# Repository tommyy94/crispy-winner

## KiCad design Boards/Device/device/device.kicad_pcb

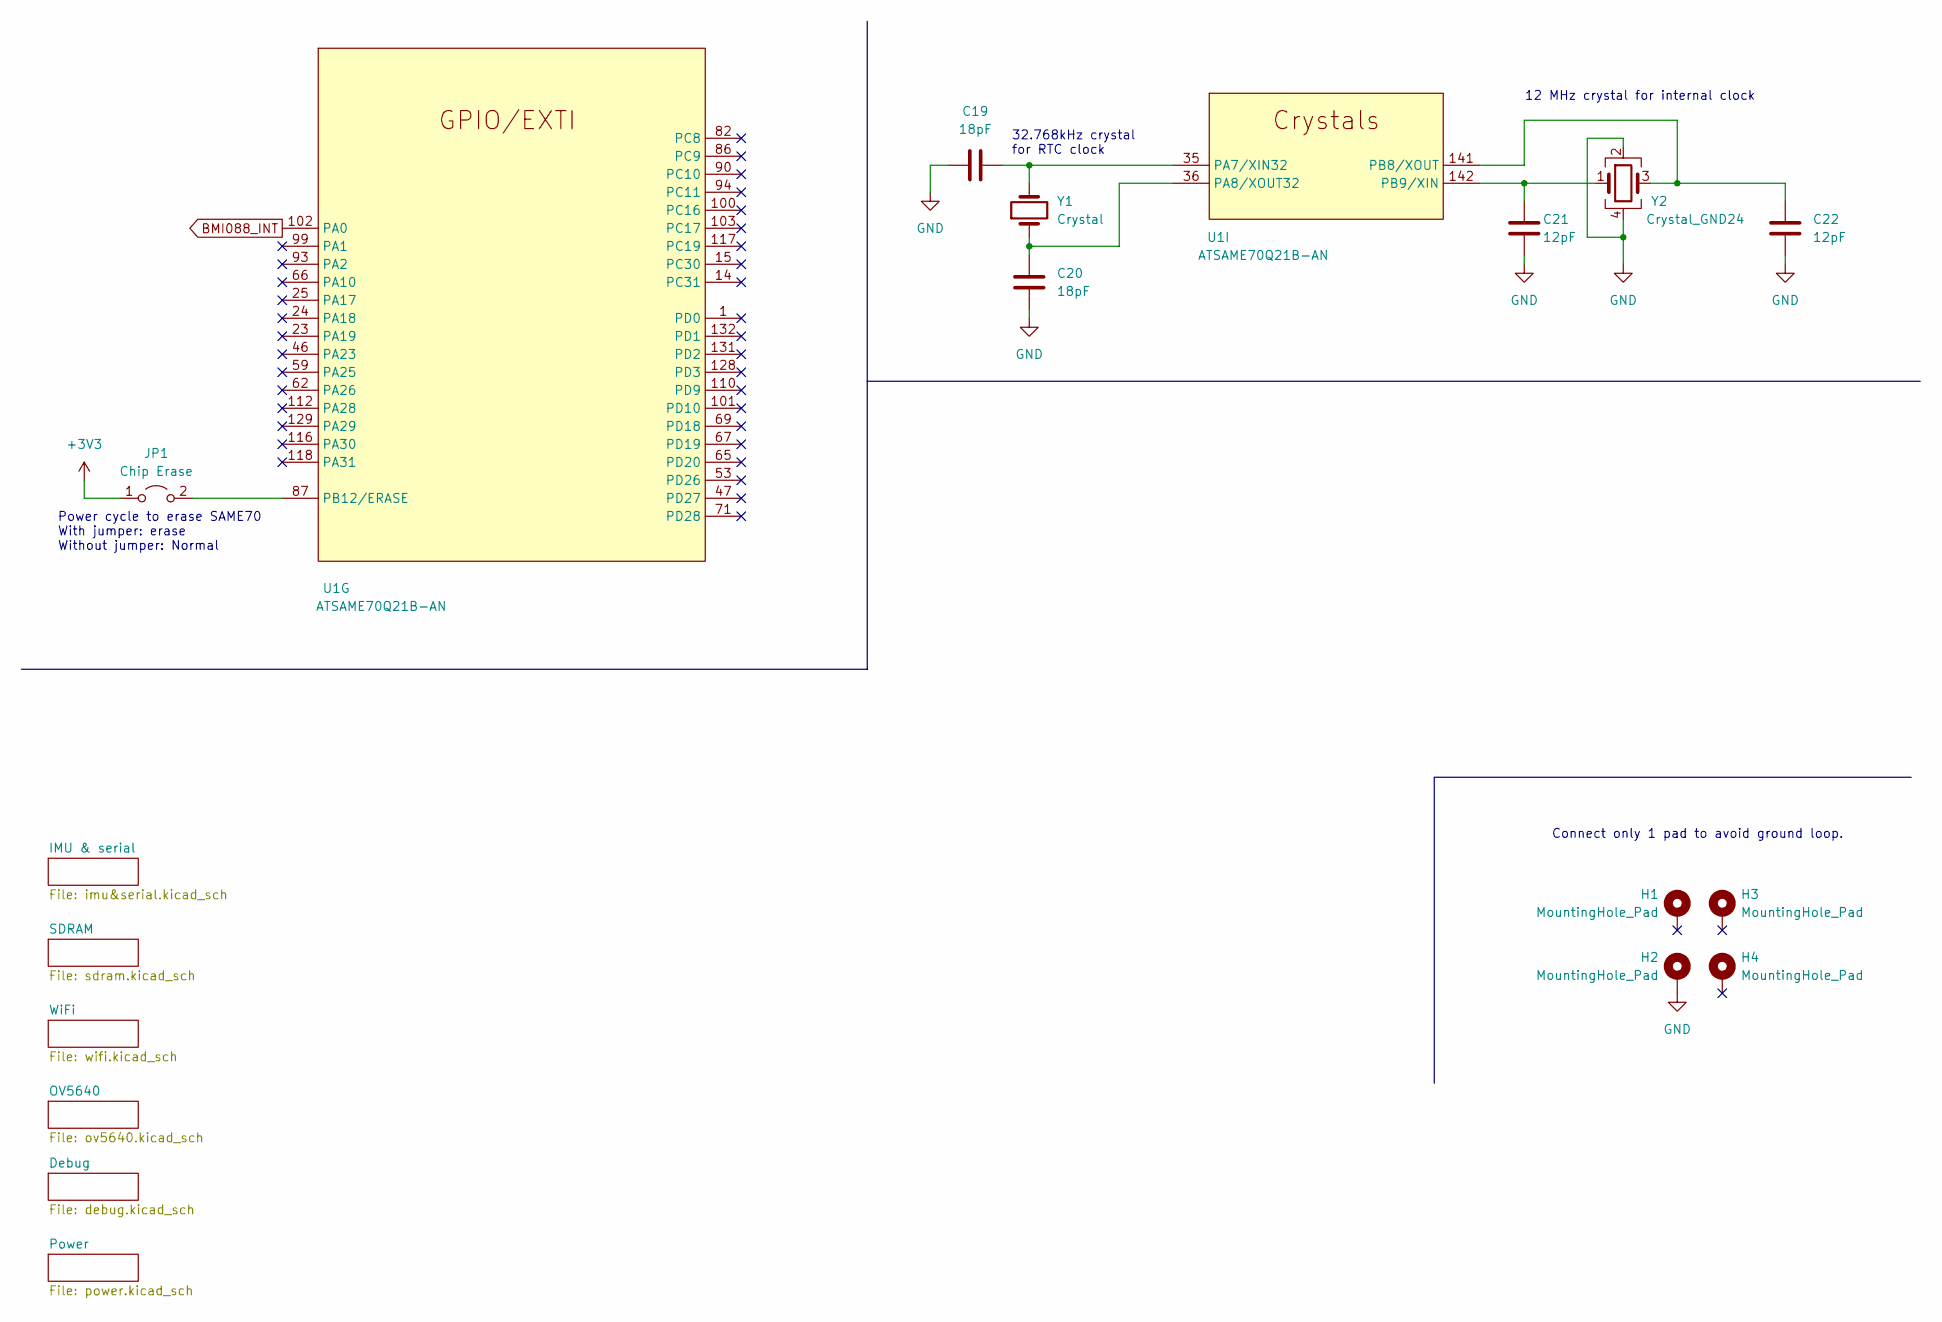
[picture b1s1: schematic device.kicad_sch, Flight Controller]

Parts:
C19, C20: 18pF; C_0603_1608Metric_Pad1.08x0.95mm_HandSolder
C21, C22: 12pF; C_0603_1608Metric_Pad1.08x0.95mm_HandSolder
H1, H2, H3, H4: MountingHole_Pad; MountingHole_3.2mm_M3_Pad
JP1: Chip Erase; PinHeader_1x02_P2.54mm_Vertical
U1: ATSAME70Q21B-AN; LQFP-144_20x20mm_P0.5mm
Y1: Crystal; Crystal_SMD_0603-2Pin_6.0x3.5mm_HandSoldering
Y2: Crystal_GND24; Crystal_SMD_0603-4Pin_6.0x3.5mm_HandSoldering

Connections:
+3V3: JP1.1 (A); also elsewhere on the board
BMI088_INT: U1.102 (PA0); also elsewhere on the board
GND: C19.1, C20.1, C21.2, C22.2, H2.1, Y2.2, Y2.4; also elsewhere on the board
unnamed: C19.2, U1.35 (PA7/XIN32), Y1.2
unnamed: C20.2, U1.36 (PA8/XOUT32), Y1.1
unnamed: C21.1, U1.142 (PB9/XIN), Y2.1
unnamed: C22.1, U1.141 (PB8/XOUT), Y2.3
unnamed: JP1.2 (B), U1.87 (PB12/ERASE)

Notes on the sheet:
Connect only 1 pad to avoid ground loop.
12 MHz crystal for internal clock
32.768kHz crystal for RTC clock
Power cycle to erase SAME70 With jumper: erase Without jumper: Normal

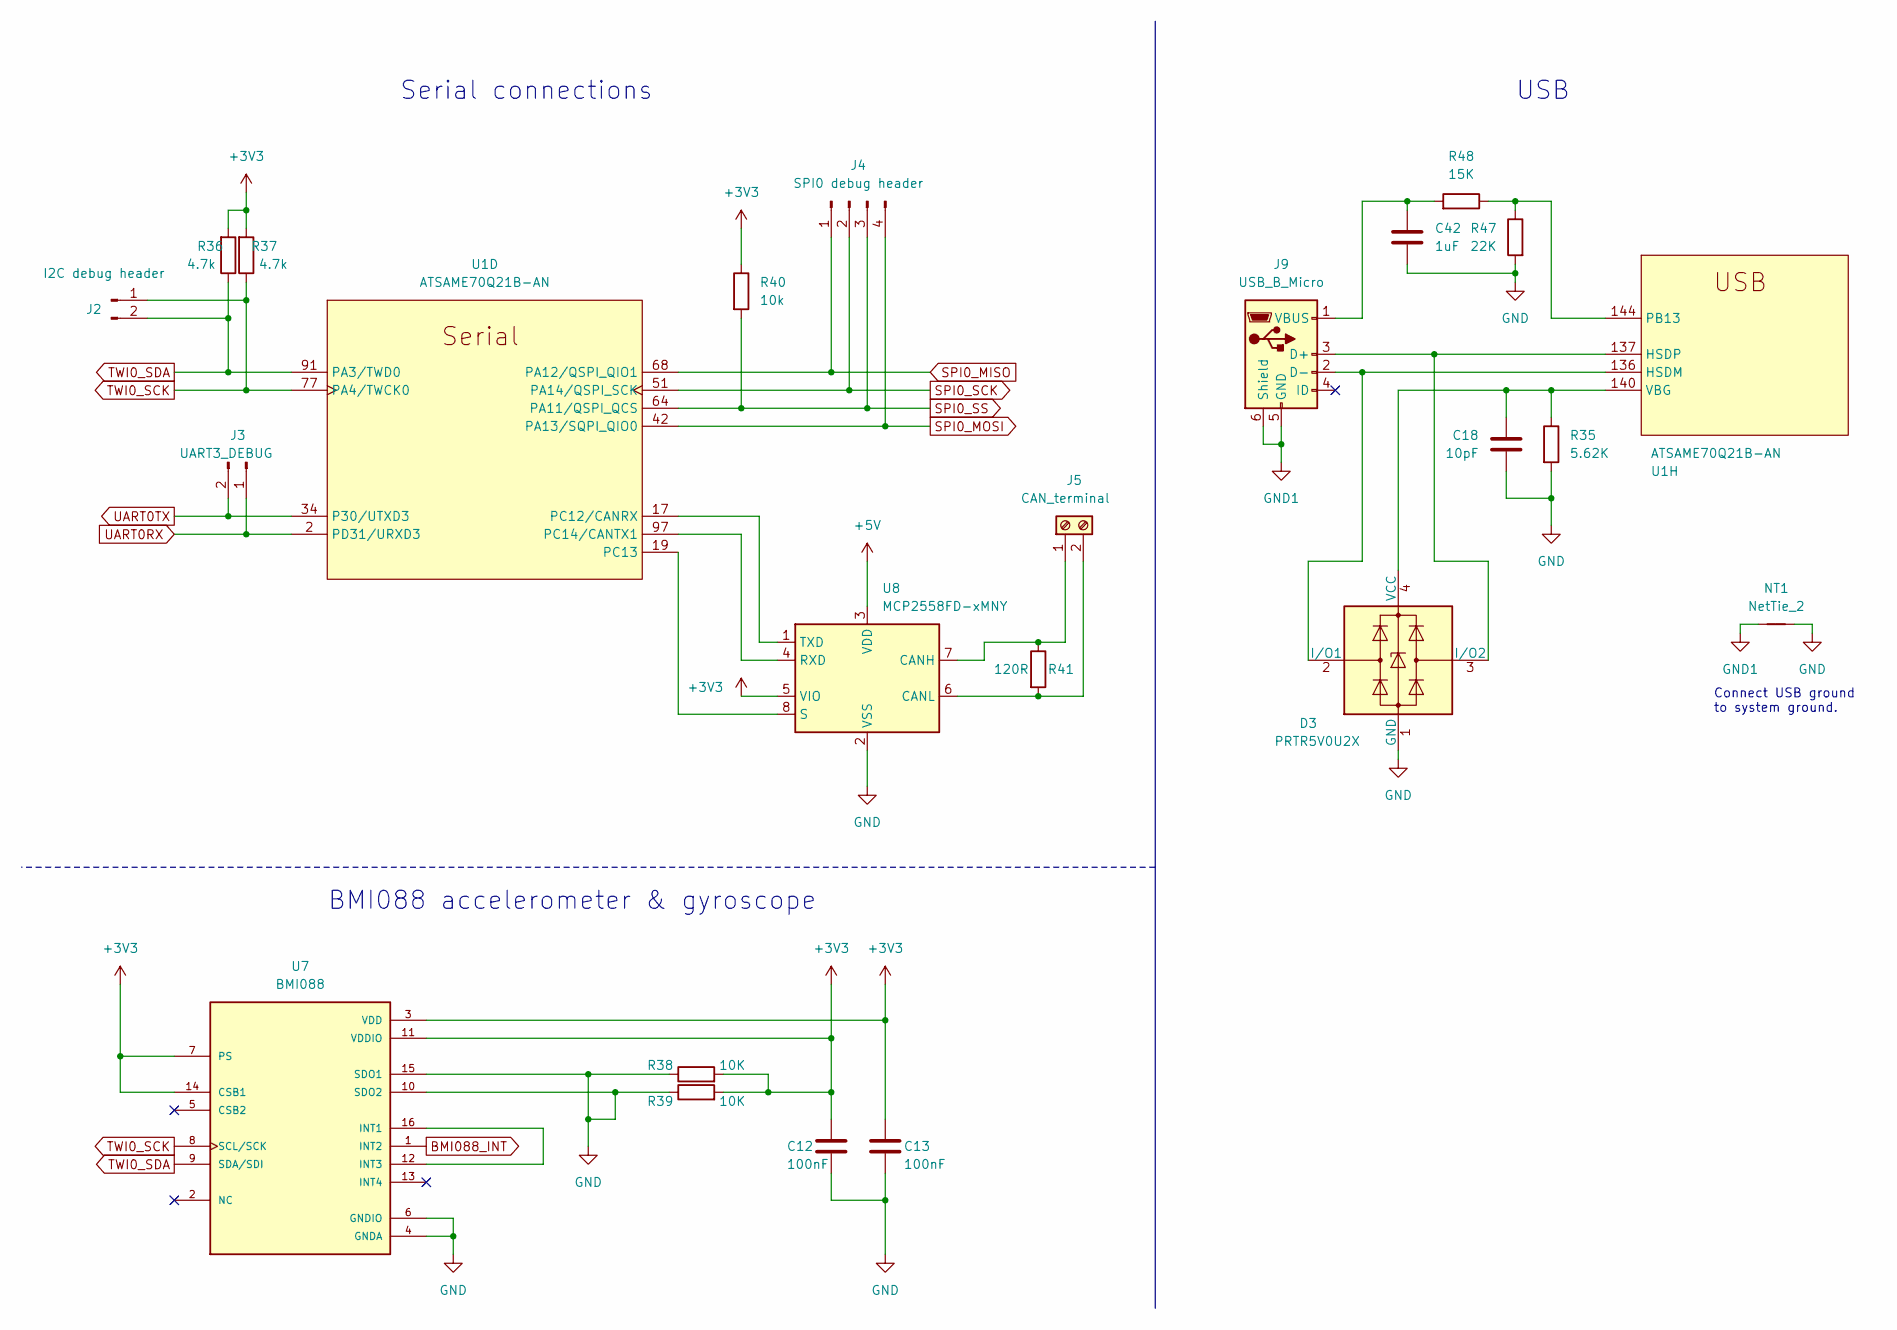
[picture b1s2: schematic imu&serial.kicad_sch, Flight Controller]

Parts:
C12, C13: 100nF; C_0603_1608Metric_Pad1.08x0.95mm_HandSolder
C18: 10pF; C_0603_1608Metric_Pad1.08x0.95mm_HandSolder
C42: 1uF; C_0603_1608Metric_Pad1.08x0.95mm_HandSolder
D3: PRTR5V0U2X; SOT-143
J2: I2C debug header; PinHeader_1x02_P2.54mm_Vertical
J3: UART3_DEBUG; PinHeader_1x02_P2.54mm_Vertical
J4: SPI0 debug header; PinHeader_1x04_P2.54mm_Vertical
J5: CAN_terminal; TerminalBlock_Altech_AK300-2_P5.00mm
J9: USB_B_Micro; USB_Micro-B_Wuerth_614105150721_Vertical
NT1: NetTie_2; NetTie-2_SMD_Pad2.0mm
R35: 5.62K; R_0201_0603Metric_Pad0.64x0.40mm_HandSolder
R36, R37: 4.7k; R_0201_0603Metric_Pad0.64x0.40mm_HandSolder
R38, R39: 10K; R_0201_0603Metric_Pad0.64x0.40mm_HandSolder
R40: 10k; R_0201_0603Metric_Pad0.64x0.40mm_HandSolder
R41: 120R; R_0201_0603Metric_Pad0.64x0.40mm_HandSolder
R47: 22K; R_0201_0603Metric_Pad0.64x0.40mm_HandSolder
R48: 15K; R_0201_0603Metric_Pad0.64x0.40mm_HandSolder
U1: ATSAME70Q21B-AN; LQFP-144_20x20mm_P0.5mm
U7: BMI088; PQFN50P450X300X100-16N
U8: MCP2558FD-xMNY; TDFN-8-1EP_3x2mm_P0.5mm_EP1.80x1.65mm

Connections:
+3V3: C12.1, C13.1, R36.2, R37.2, R38.2, R39.2, R40.1, U7.3 (VDD), U7.7 (PS), U7.11 (VDDIO), U7.14 (CSB1), U8.5 (VIO); also elsewhere on the board
+5V: U8.3 (VDD); also elsewhere on the board
BMI088_INT: U7.1 (INT2); also elsewhere on the board
GND: C12.2, C13.2, C18.1, C42.2, D3.1 (GND), NT1.2, R35.2, R38.1, R39.1, R47.2, U7.4 (GNDA), U7.6 (GNDIO), U7.10 (SDO2), U7.15 (SDO1), U8.2 (VSS), U8.9 (VSS); also elsewhere on the board
GND1: J9.5 (GND), J9.6 (Shield), NT1.1
unnamed: C18.2, D3.4 (VCC), R35.1, U1.140 (VBG)
unnamed: D3.2 (I/O1), J9.2 (D-), U1.136 (HSDM)
unnamed: D3.3 (I/O2), J9.3 (D+), U1.137 (HSDP)
unnamed: J5.1, R41.1, U8.7 (CANH)
unnamed: J5.2, R41.2, U8.6 (CANL)
unnamed: C42.1, J9.1 (VBUS), R48.2
unnamed: R47.1, R48.1, U1.144 (PB13)
unnamed: U1.17 (PC12/CANRX), U8.1 (TXD)
unnamed: U1.19 (PC13), U8.8 (S)
unnamed: U1.97 (PC14/CANTX1), U8.4 (RXD)
unnamed: U7.12 (INT3), U7.16 (INT1)
SPI0_MISO: J4.1, U1.68 (PA12/QSPI_QIO1); also elsewhere on the board
SPI0_MOSI: J4.4, U1.42 (PA13/SQPI_QIO0); also elsewhere on the board
SPI0_SCK: J4.2, U1.51 (PA14/QSPI_SCK); also elsewhere on the board
SPI0_SS: J4.3, R40.2, U1.64 (PA11/QSPI_QCS); also elsewhere on the board
TWI0_SCK: J2.1, R37.1, U1.77 (PA4/TWCK0), U7.8 (SCL/SCK); also elsewhere on the board
TWI0_SDA: J2.2, R36.1, U1.91 (PA3/TWD0), U7.9 (SDA/SDI); also elsewhere on the board
UART0RX: J3.1, U1.2 (PD31/URXD3); also elsewhere on the board
UART0TX: J3.2, U1.34 (P30/UTXD3); also elsewhere on the board

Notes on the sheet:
USB
BMI088 accelerometer & gyroscope
Connect USB ground to system ground.
Serial connections

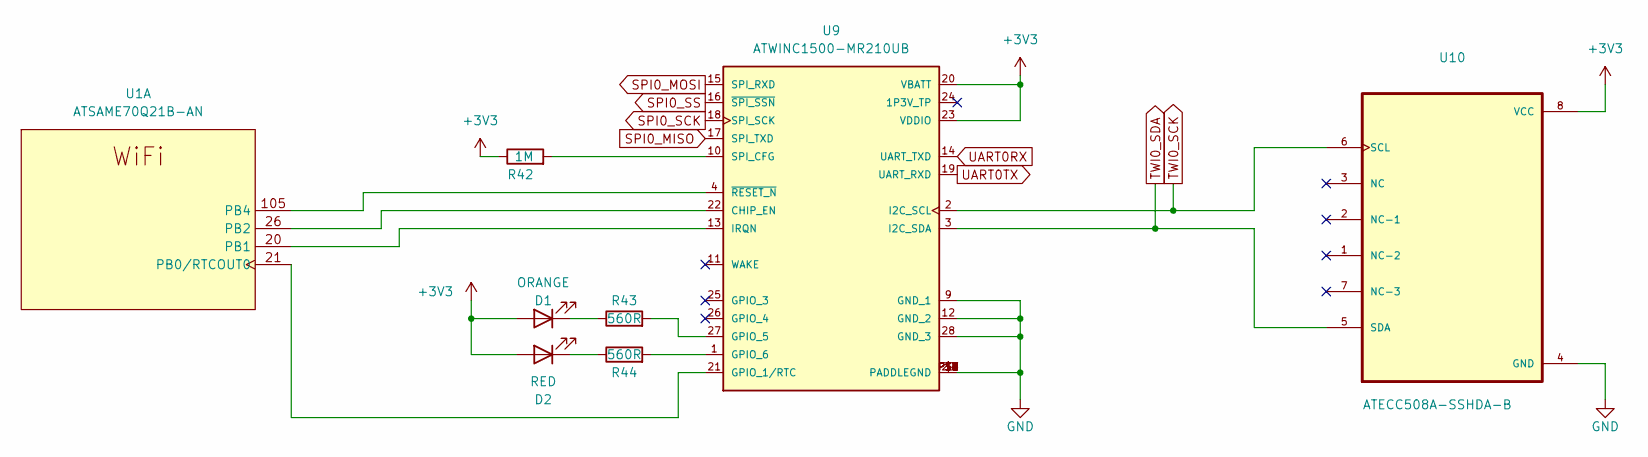
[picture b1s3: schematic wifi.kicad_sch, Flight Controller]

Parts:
D1: ORANGE; LED_2010_5025Metric_Pad1.52x2.65mm_HandSolder
D2: RED; LED_2010_5025Metric_Pad1.52x2.65mm_HandSolder
R42: 1M; R_0201_0603Metric_Pad0.64x0.40mm_HandSolder
R43, R44: 560R; R_0201_0603Metric_Pad0.64x0.40mm_HandSolder
U1: ATSAME70Q21B-AN; LQFP-144_20x20mm_P0.5mm
U9: ATWINC1500-MR210UB; MICROCHIP_ATWINC1500-MR210UB
U10: ATECC508A-SSHDA-B; SOIC127P600X175-8N

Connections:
+3V3: D1.2 (A), D2.2 (A), R42.1, U9.20 (VBATT), U9.23 (VDDIO), U10.8 (VCC); also elsewhere on the board
GND: U9.9 (GND_1), U9.12 (GND_2), U9.28 (GND_3), U9.29 (PADDLEGND), U9.P$1 (PADDLEGND), U9.P$2 (PADDLEGND), U9.P$3 (PADDLEGND), U9.P$4 (PADDLEGND), U9.P$5 (PADDLEGND), U9.P$6 (PADDLEGND), U9.P$7 (PADDLEGND), U9.P$8 (PADDLEGND), U9.P$9 (PADDLEGND), U10.4 (GND); also elsewhere on the board
unnamed: D1.1 (K), R43.1
unnamed: D2.1 (K), R44.1
unnamed: R42.2, U9.10 (SPI_CFG)
unnamed: R43.2, U9.27 (GPIO_5)
unnamed: R44.2, U9.1 (GPIO_6)
unnamed: U1.20 (PB1), U9.13 (IRQN)
unnamed: U1.21 (PB0/RTCOUT0), U9.21 (GPIO_1/RTC)
unnamed: U1.26 (PB2), U9.22 (CHIP_EN)
unnamed: U1.105 (PB4), U9.4 (~RESET_N)
SPI0_MISO: U9.17 (SPI_TXD); also elsewhere on the board
SPI0_MOSI: U9.15 (SPI_RXD); also elsewhere on the board
SPI0_SCK: U9.18 (SPI_SCK); also elsewhere on the board
SPI0_SS: U9.16 (~SPI_SSN); also elsewhere on the board
TWI0_SCK: U9.2 (I2C_SCL), U10.6 (SCL); also elsewhere on the board
TWI0_SDA: U9.3 (I2C_SDA), U10.5 (SDA); also elsewhere on the board
UART0RX: U9.14 (UART_TXD); also elsewhere on the board
UART0TX: U9.19 (UART_RXD); also elsewhere on the board

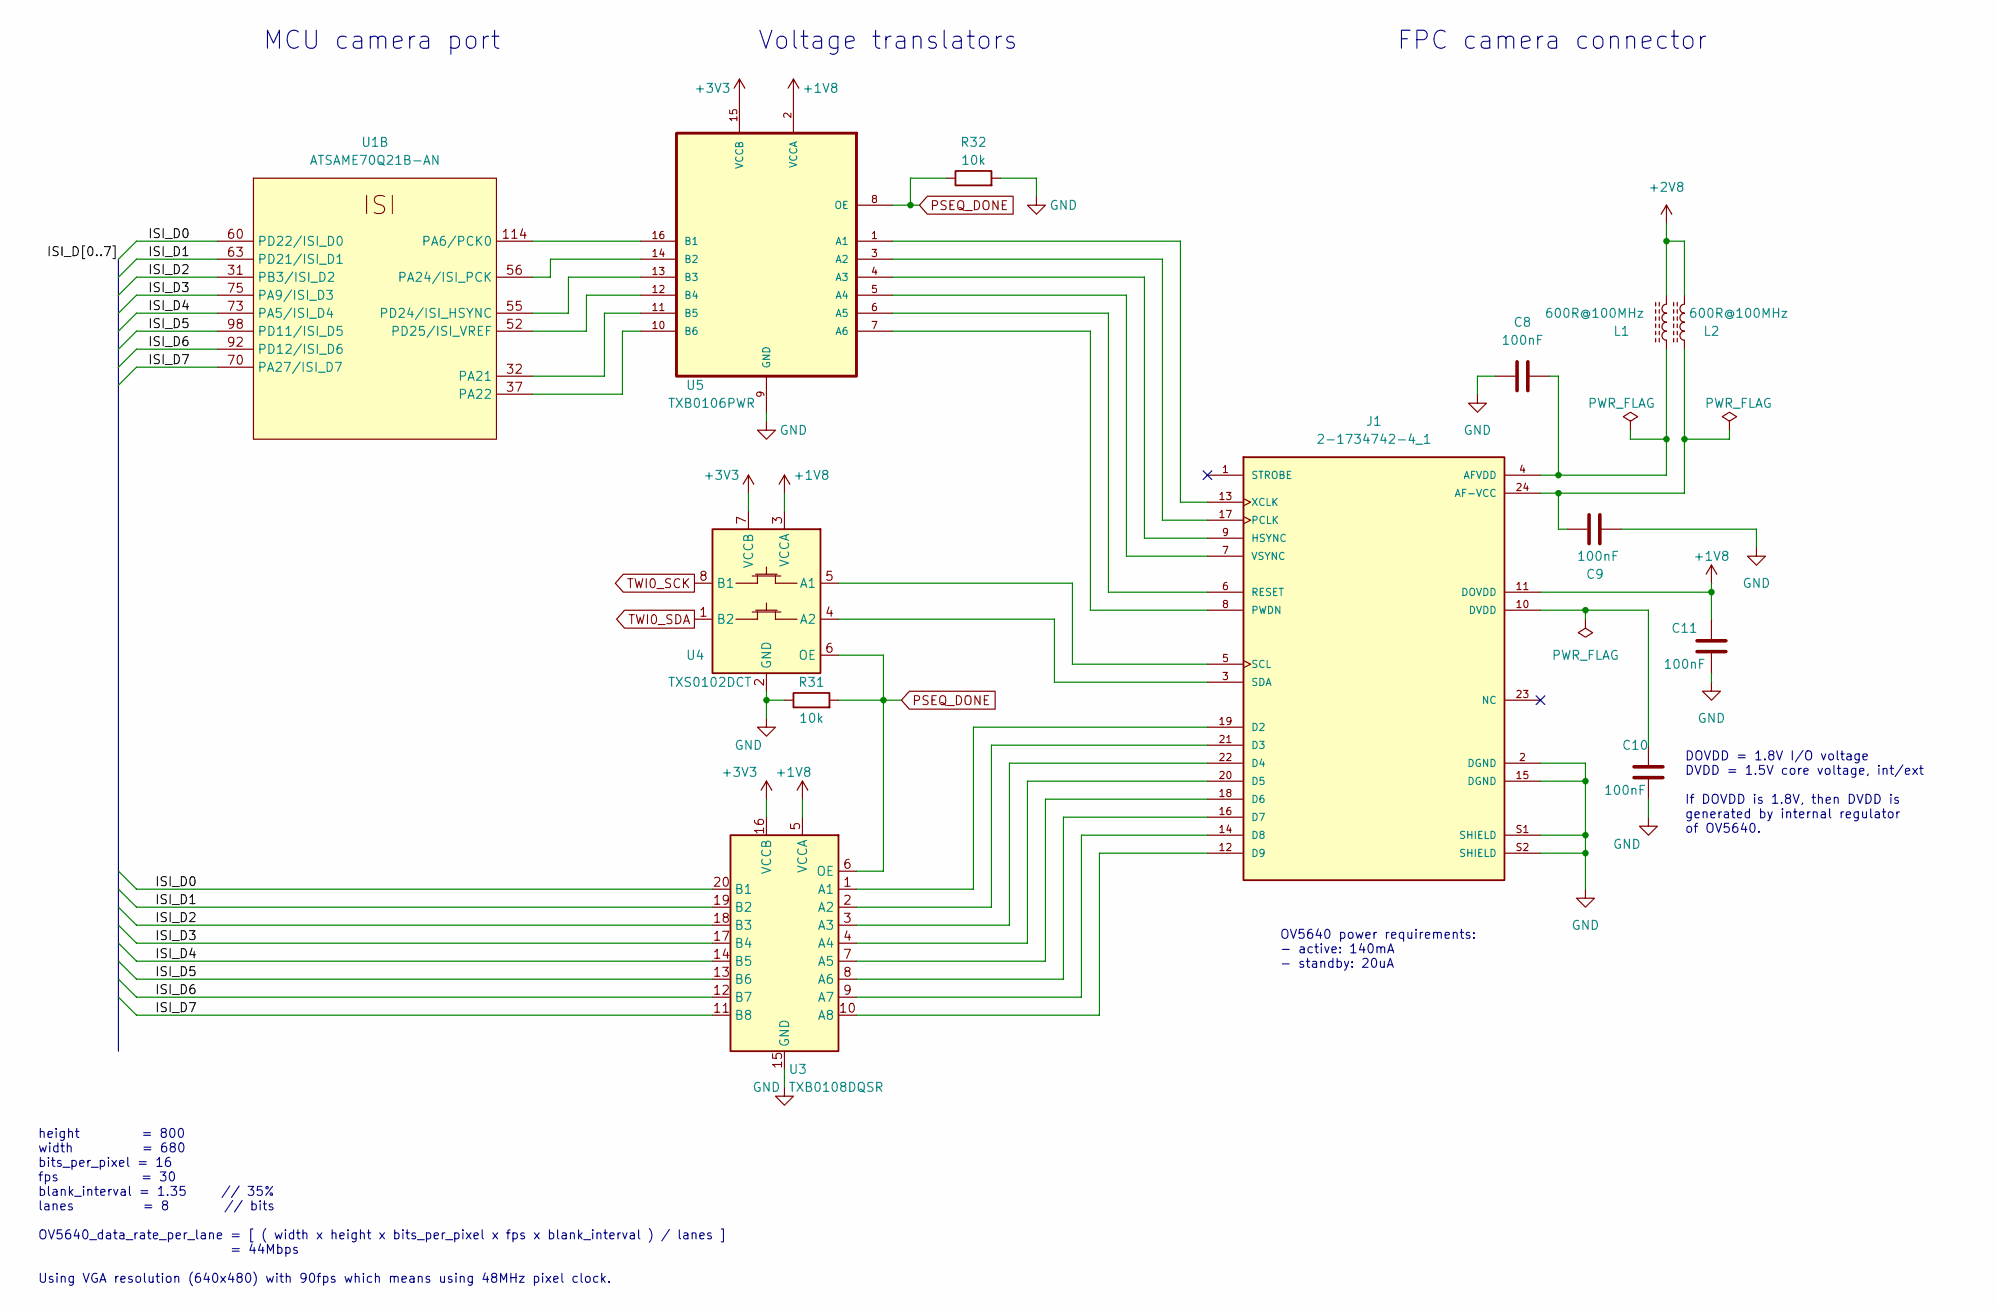
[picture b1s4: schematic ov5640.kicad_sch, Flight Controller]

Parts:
C8, C9, C10, C11: 100nF; C_0603_1608Metric_Pad1.08x0.95mm_HandSolder
J1: 2-1734742-4_1; TE_2-1734742-4
L1, L2: 600R@100MHz; L_1206_3216Metric_Pad1.42x1.75mm_HandSolder
R31, R32: 10k; R_0201_0603Metric_Pad0.64x0.40mm_HandSolder
U1: ATSAME70Q21B-AN; LQFP-144_20x20mm_P0.5mm
U3: TXB0108DQSR; USON-20_2x4mm_P0.4mm
U4: TXS0102DCT; SSOP-8_2.95x2.8mm_P0.65mm
U5: TXB0106PWR; SOP65P640X120-16N

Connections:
+1V8: C11.2, J1.11 (DOVDD), U3.5 (VCCA), U4.3 (VCCA), U5.2 (VCCA); also elsewhere on the board
+2V8: L1.2, L2.2; also elsewhere on the board
+3V3: U3.16 (VCCB), U4.7 (VCCB), U5.15 (VCCB); also elsewhere on the board
/OV5640/ISI_D0: U1.60 (PD22/ISI_D0), U3.20 (B1)
/OV5640/ISI_D1: U1.63 (PD21/ISI_D1), U3.19 (B2)
/OV5640/ISI_D2: U1.31 (PB3/ISI_D2), U3.18 (B3)
/OV5640/ISI_D3: U1.75 (PA9/ISI_D3), U3.17 (B4)
/OV5640/ISI_D4: U1.73 (PA5/ISI_D4), U3.14 (B5)
/OV5640/ISI_D5: U1.98 (PD11/ISI_D5), U3.13 (B6)
/OV5640/ISI_D6: U1.92 (PD12/ISI_D6), U3.12 (B7)
/OV5640/ISI_D7: U1.70 (PA27/ISI_D7), U3.11 (B8)
GND: C8.2, C9.2, C10.1, C11.1, J1.2 (DGND), J1.15 (DGND), J1.S1 (SHIELD), J1.S2 (SHIELD), R31.1, R32.2, U3.15 (GND), U4.2 (GND), U5.9 (GND); also elsewhere on the board
unnamed: C8.1, J1.4 (AFVDD), L1.1
unnamed: C9.1, J1.24 (AF-VCC), L2.1
unnamed: C10.2, J1.10 (DVDD)
unnamed: J1.3 (SDA), U4.4 (A2)
unnamed: J1.5 (SCL), U4.5 (A1)
unnamed: J1.6 (RESET), U5.6 (A5)
unnamed: J1.7 (VSYNC), U5.5 (A4)
unnamed: J1.8 (PWDN), U5.7 (A6)
unnamed: J1.9 (HSYNC), U5.4 (A3)
unnamed: J1.12 (D9), U3.10 (A8)
unnamed: J1.13 (XCLK), U5.1 (A1)
unnamed: J1.14 (D8), U3.9 (A7)
unnamed: J1.16 (D7), U3.8 (A6)
unnamed: J1.17 (PCLK), U5.3 (A2)
unnamed: J1.18 (D6), U3.7 (A5)
unnamed: J1.19 (D2), U3.1 (A1)
unnamed: J1.20 (D5), U3.4 (A4)
unnamed: J1.21 (D3), U3.2 (A2)
unnamed: J1.22 (D4), U3.3 (A3)
unnamed: U1.32 (PA21), U5.11 (B5)
unnamed: U1.37 (PA22), U5.10 (B6)
unnamed: U1.52 (PD25/ISI_VREF), U5.12 (B4)
unnamed: U1.55 (PD24/ISI_HSYNC), U5.13 (B3)
unnamed: U1.56 (PA24/ISI_PCK), U5.14 (B2)
unnamed: U1.114 (PA6/PCK0), U5.16 (B1)
PSEQ_DONE: R31.2, R32.1, U3.6 (OE), U4.6 (OE), U5.8 (OE); also elsewhere on the board
TWI0_SCK: U4.8 (B1); also elsewhere on the board
TWI0_SDA: U4.1 (B2); also elsewhere on the board

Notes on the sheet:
FPC camera connector
DOVDD = 1.8V I/O voltage DVDD = 1.5V core voltage, int/ext If DOVDD is 1.8V, then DVDD is generated by internal regulator of OV5640.
height = 800 width = 680 bits_per_pixel = 16 fps = 30 blank_interval = 1.35 // 35% lanes = 8 // bits OV5640_data_rate_per_lane = [ ( width x height x bits_per_pixel x fps x blank_interval ) / lanes ] = 44Mbps Using VGA resolution (640x480) with 90fps which means using 48MHz pixel clock.
MCU camera port
Voltage translators
OV5640 power requirements: - active: 140mA - standby: 20uA

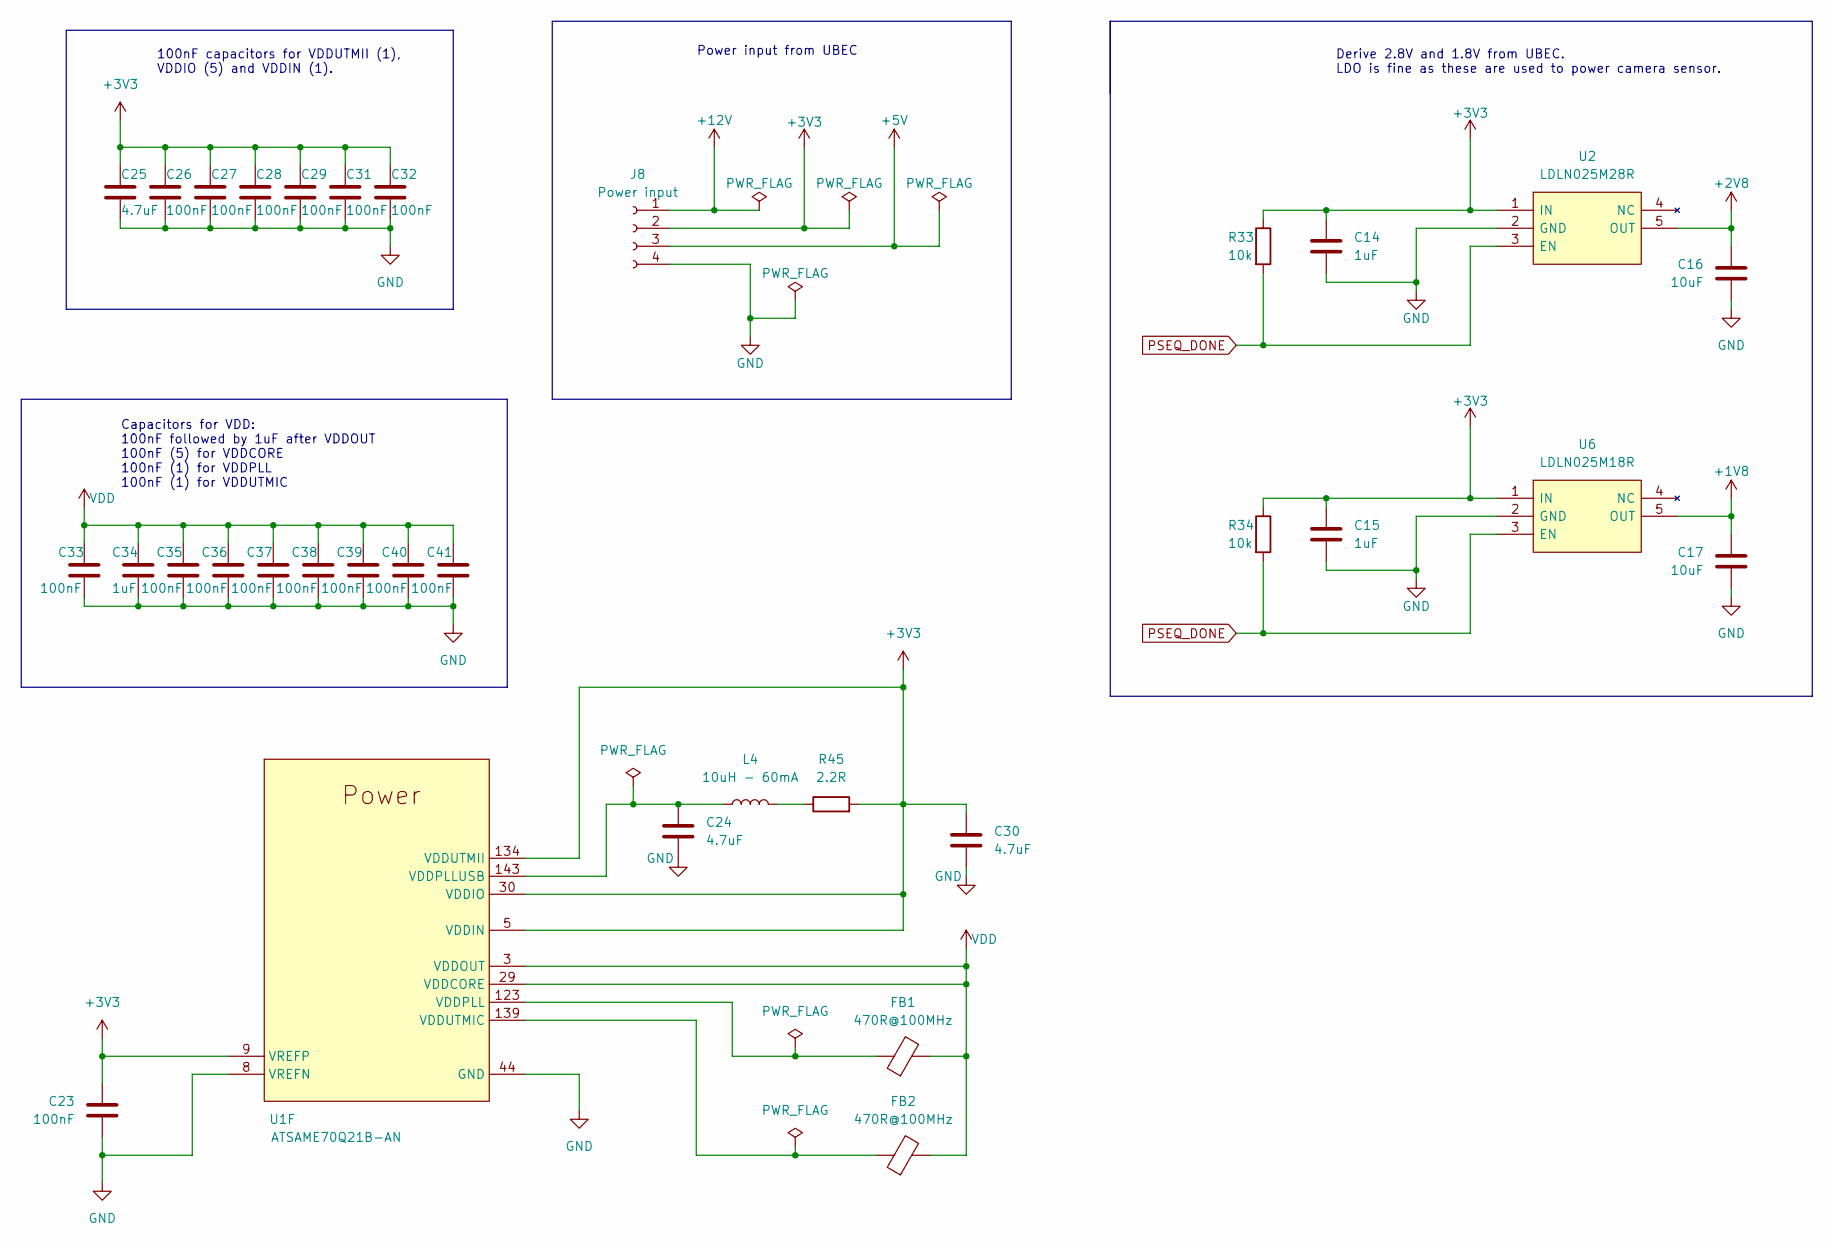
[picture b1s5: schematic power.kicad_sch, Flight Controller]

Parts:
C14, C15, C34: 1uF; C_0603_1608Metric_Pad1.08x0.95mm_HandSolder
C16, C17: 10uF; C_0603_1608Metric_Pad1.08x0.95mm_HandSolder
C23, C26, C27, C28, C29, C31, C32, C33, C35, C36, C37, C38, C39, C40, C41: 100nF; C_0603_1608Metric_Pad1.08x0.95mm_HandSolder
C24, C25, C30: 4.7uF; C_0603_1608Metric_Pad1.08x0.95mm_HandSolder
FB1, FB2: 470R@100MHz; LairdTech_28C0236-0JW-10
J8: Power input; PinSocket_1x04_P2.54mm_Vertical
L4: 10uH - 60mA; L_1206_3216Metric_Pad1.42x1.75mm_HandSolder
R33, R34: 10k; R_0201_0603Metric_Pad0.64x0.40mm_HandSolder
R45: 2.2R; R_0201_0603Metric_Pad0.64x0.40mm_HandSolder
U1: ATSAME70Q21B-AN; LQFP-144_20x20mm_P0.5mm
U2: LDLN025M28R; SOT95P280X145-5N; Mouser Part Number 511-LDLN025M28R
U6: LDLN025M18R; SOT95P280X145-5N; Mouser Part Number 511-LDLN025M18R

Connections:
+1V8: C17.2, U6.5 (OUT); also elsewhere on the board
+2V8: C16.2, U2.5 (OUT); also elsewhere on the board
+3V3: C14.1, C15.1, C23.2, C25.1, C26.1, C27.1, C28.1, C29.1, C30.1, C31.1, C32.1, J8.2, R33.1, R34.1, R45.2, U1.5 (VDDIN), U1.9 (VREFP), U1.30 (VDDIO), U1.43 (VDDIO), U1.72 (VDDIO), U1.80 (VDDIO), U1.96 (VDDIO), U1.134 (VDDUTMII), U2.1 (IN), U6.1 (IN); also elsewhere on the board
+5V: J8.3; also elsewhere on the board
+12V: J8.1
GND: C14.2, C15.2, C16.1, C17.1, C23.1, C24.2, C25.2, C26.2, C27.2, C28.2, C29.2, C30.2, C31.2, C32.2, C33.2, C34.2, C35.2, C36.2, C37.2, C38.2, C39.2, C40.2, C41.2, J8.4, U1.8 (VREFN), U1.44 (GND), U1.61 (GND), U1.95 (GND), U1.115 (GND), U1.135 (GND), U1.138 (GND), U2.2 (GND), U6.2 (GND); also elsewhere on the board
unnamed: C24.1, L4.1, U1.143 (VDDPLLUSB)
unnamed: FB1.1, U1.123 (VDDPLL)
unnamed: FB2.1, U1.139 (VDDUTMIC)
unnamed: L4.2, R45.1
PSEQ_DONE: R33.2, R34.2, U2.3 (EN), U6.3 (EN); also elsewhere on the board
VDD: C33.1, C34.1, C35.1, C36.1, C37.1, C38.1, C39.1, C40.1, C41.1, FB1.2, FB2.2, U1.3 (VDDOUT), U1.29 (VDDCORE), U1.33 (VDDCORE), U1.50 (VDDCORE), U1.81 (VDDCORE), U1.107 (VDDCORE)

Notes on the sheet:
Capacitors for VDD: 100nF followed by 1uF after VDDOUT 100nF (5) for VDDCORE 100nF (1) for VDDPLL 100nF (1) for VDDUTMIC
Power input from UBEC
100nF capacitors for VDDUTMII (1), VDDIO (5) and VDDIN (1).
Derive 2.8V and 1.8V from UBEC. LDO is fine as these are used to power camera sensor.

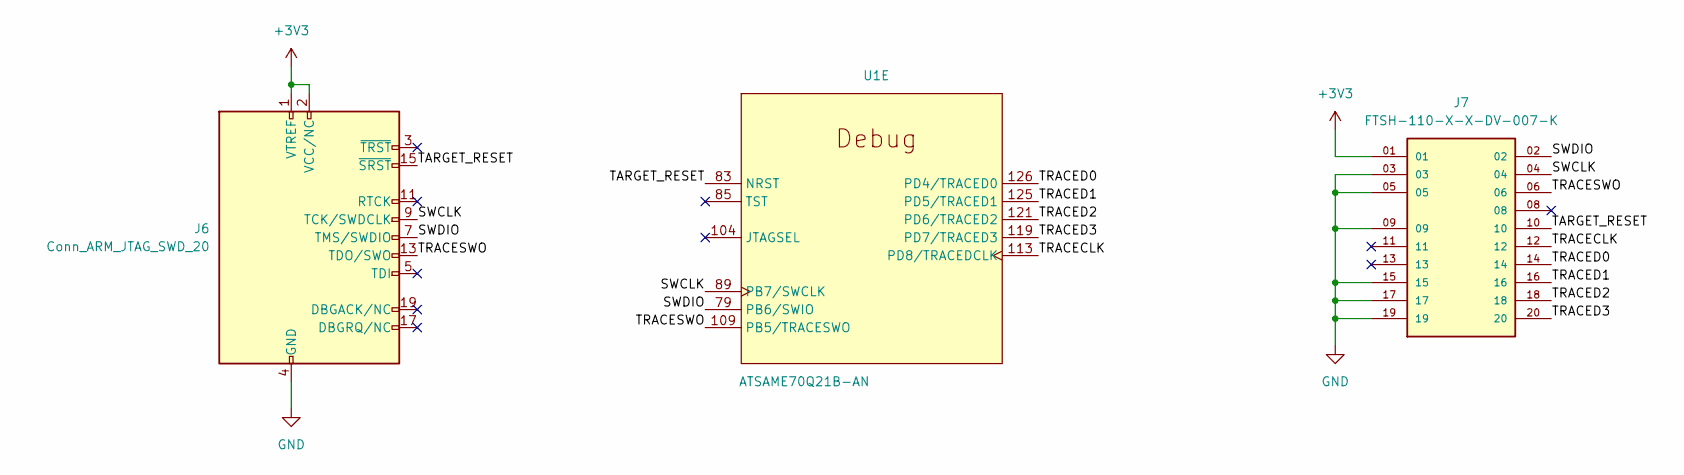
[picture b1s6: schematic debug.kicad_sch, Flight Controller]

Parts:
J6: Conn_ARM_JTAG_SWD_20
J7: FTSH-110-X-X-DV-007-K; SAMTEC_FTSH-110-X-X-DV-007-K; PARTREV H
U1: ATSAME70Q21B-AN; LQFP-144_20x20mm_P0.5mm

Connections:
+3V3: J6.1 (VTREF), J6.2 (VCC/NC), J7.01; also elsewhere on the board
/Debug/SWCLK: J6.9 (TCK/SWDCLK), J7.04, U1.89 (PB7/SWCLK)
/Debug/SWDIO: J6.7 (TMS/SWDIO), J7.02, U1.79 (PB6/SWIO)
/Debug/TARGET_RESET: J6.15 (~SRST), J7.10, U1.83 (NRST)
/Debug/TRACECLK: J7.12, U1.113 (PD8/TRACEDCLK)
/Debug/TRACED0: J7.14, U1.126 (PD4/TRACED0)
/Debug/TRACED1: J7.16, U1.125 (PD5/TRACED1)
/Debug/TRACED2: J7.18, U1.121 (PD6/TRACED2)
/Debug/TRACED3: J7.20, U1.119 (PD7/TRACED3)
/Debug/TRACESWO: J6.13 (TDO/SWO), J7.06, U1.109 (PB5/TRACESWO)
GND: J6.4 (GND), J6.6 (GND), J6.8 (GND), J6.10 (GND), J6.12 (GND), J6.14 (GND), J6.16 (GND), J6.18 (GND), J6.20 (GND), J7.03, J7.05, J7.09, J7.15, J7.17, J7.19; also elsewhere on the board

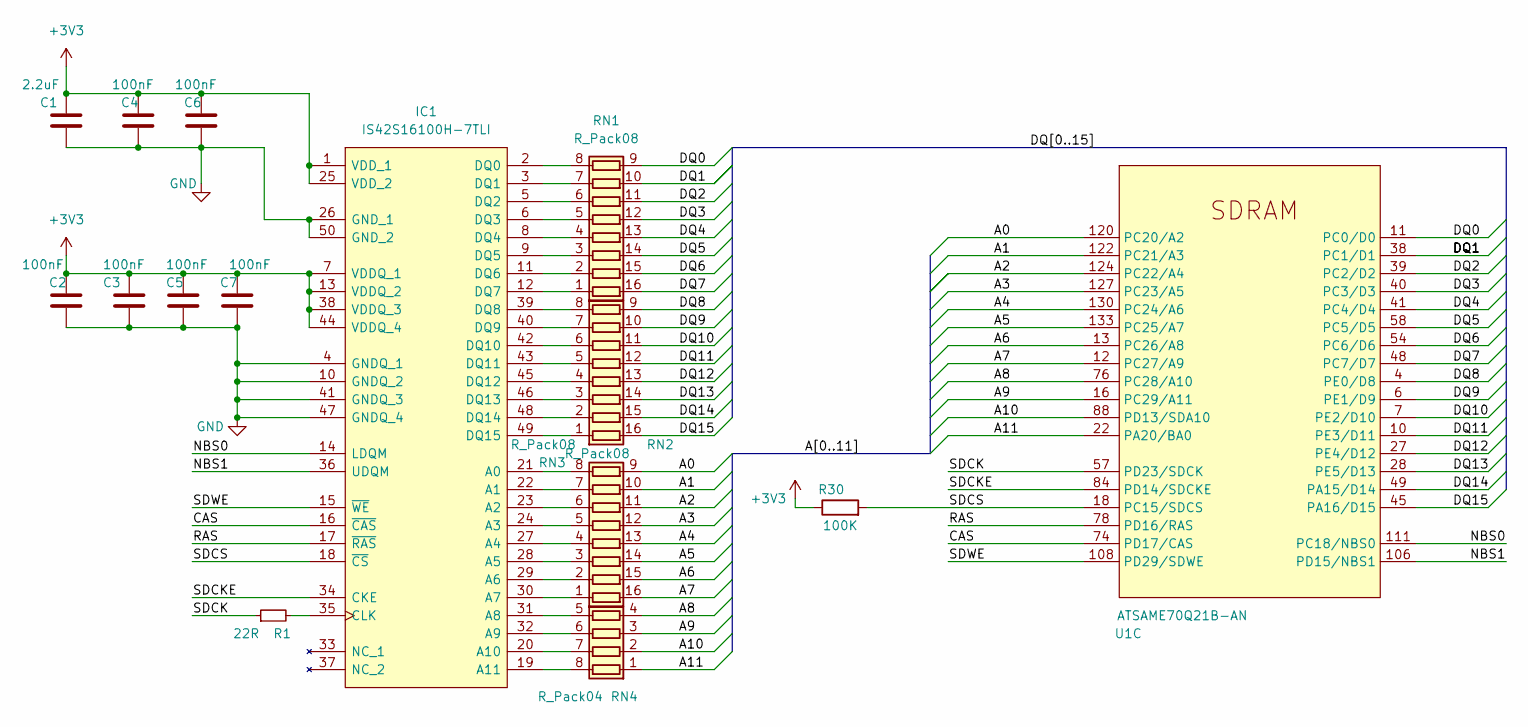
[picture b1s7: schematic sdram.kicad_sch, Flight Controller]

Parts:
C1: 2.2uF; C_0603_1608Metric_Pad1.08x0.95mm_HandSolder
C2, C3, C4, C5, C6, C7: 100nF; C_0603_1608Metric_Pad1.08x0.95mm_HandSolder
IC1: IS42S16100H-7TLI; SOP80P1176X120-50N; Mouser Part Number 870-IS42S16100H-7TLI
R1: 22R; R_0201_0603Metric_Pad0.64x0.40mm_HandSolder
R30: 100K; R_0201_0603Metric_Pad0.64x0.40mm_HandSolder
RN1, RN2, RN3: R_Pack08; R_Array_Convex_8x0602
RN4: R_Pack04; R_Array_Convex_4x0603
U1: ATSAME70Q21B-AN; LQFP-144_20x20mm_P0.5mm

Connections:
+3V3: C1.1, C2.1, C3.1, C4.1, C5.1, C6.1, C7.1, IC1.1 (VDD_1), IC1.7 (VDDQ_1), IC1.13 (VDDQ_2), IC1.25 (VDD_2), IC1.38 (VDDQ_3), IC1.44 (VDDQ_4), R30.1; also elsewhere on the board
/SDRAM/A0: RN3.9 (R8.2), U1.120 (PC20/A2)
/SDRAM/A1: RN3.10 (R7.2), U1.122 (PC21/A3)
/SDRAM/A2: RN3.11 (R6.2), U1.124 (PC22/A4)
/SDRAM/A3: RN3.12 (R5.2), U1.127 (PC23/A5)
/SDRAM/A4: RN3.13 (R4.2), U1.130 (PC24/A6)
/SDRAM/A5: RN3.14 (R3.2), U1.133 (PC25/A7)
/SDRAM/A6: RN3.15 (R2.2), U1.13 (PC26/A8)
/SDRAM/A7: RN3.16 (R1.2), U1.12 (PC27/A9)
/SDRAM/A8: RN4.4 (R4.1), U1.76 (PC28/A10)
/SDRAM/A9: RN4.3 (R3.1), U1.16 (PC29/A11)
/SDRAM/A10: RN4.2 (R2.1), U1.88 (PD13/SDA10)
/SDRAM/A11: RN4.1 (R1.1), U1.22 (PA20/BA0)
/SDRAM/CAS: IC1.16 (~CAS), U1.74 (PD17/CAS)
/SDRAM/DQ0: RN1.9 (R8.2), U1.11 (PC0/D0)
/SDRAM/DQ1: RN1.10 (R7.2), U1.38 (PC1/D1)
/SDRAM/DQ2: RN1.11 (R6.2), U1.39 (PC2/D2)
/SDRAM/DQ3: RN1.12 (R5.2), U1.40 (PC3/D3)
/SDRAM/DQ4: RN1.13 (R4.2), U1.41 (PC4/D4)
/SDRAM/DQ5: RN1.14 (R3.2), U1.58 (PC5/D5)
/SDRAM/DQ6: RN1.15 (R2.2), U1.54 (PC6/D6)
/SDRAM/DQ7: RN1.16 (R1.2), U1.48 (PC7/D7)
/SDRAM/DQ8: RN2.9 (R8.2), U1.4 (PE0/D8)
/SDRAM/DQ9: RN2.10 (R7.2), U1.6 (PE1/D9)
/SDRAM/DQ10: RN2.11 (R6.2), U1.7 (PE2/D10)
/SDRAM/DQ11: RN2.12 (R5.2), U1.10 (PE3/D11)
/SDRAM/DQ12: RN2.13 (R4.2), U1.27 (PE4/D12)
/SDRAM/DQ13: RN2.14 (R3.2), U1.28 (PE5/D13)
/SDRAM/DQ14: RN2.15 (R2.2), U1.49 (PA15/D14)
/SDRAM/DQ15: RN2.16 (R1.2), U1.45 (PA16/D15)
/SDRAM/NBS0: IC1.14 (LDQM), U1.111 (PC18/NBS0)
/SDRAM/NBS1: IC1.36 (UDQM), U1.106 (PD15/NBS1)
/SDRAM/RAS: IC1.17 (~RAS), U1.78 (PD16/RAS)
/SDRAM/SDCK: R1.1, U1.57 (PD23/SDCK)
/SDRAM/SDCKE: IC1.34 (CKE), U1.84 (PD14/SDCKE)
/SDRAM/SDCS: IC1.18 (~CS), R30.2, U1.18 (PC15/SDCS)
/SDRAM/SDWE: IC1.15 (~WE), U1.108 (PD29/SDWE)
GND: C1.2, C2.2, C3.2, C4.2, C5.2, C6.2, C7.2, IC1.4 (GNDQ_1), IC1.10 (GNDQ_2), IC1.26 (GND_1), IC1.41 (GNDQ_3), IC1.47 (GNDQ_4), IC1.50 (GND_2); also elsewhere on the board
unnamed: IC1.2 (DQ0), RN1.8 (R8.1)
unnamed: IC1.3 (DQ1), RN1.7 (R7.1)
unnamed: IC1.5 (DQ2), RN1.6 (R6.1)
unnamed: IC1.6 (DQ3), RN1.5 (R5.1)
unnamed: IC1.8 (DQ4), RN1.4 (R4.1)
unnamed: IC1.9 (DQ5), RN1.3 (R3.1)
unnamed: IC1.11 (DQ6), RN1.2 (R2.1)
unnamed: IC1.12 (DQ7), RN1.1 (R1.1)
unnamed: IC1.19 (A11), RN4.8 (R1.2)
unnamed: IC1.20 (A10), RN4.7 (R2.2)
unnamed: IC1.21 (A0), RN3.8 (R8.1)
unnamed: IC1.22 (A1), RN3.7 (R7.1)
unnamed: IC1.23 (A2), RN3.6 (R6.1)
unnamed: IC1.24 (A3), RN3.5 (R5.1)
unnamed: IC1.27 (A4), RN3.4 (R4.1)
unnamed: IC1.28 (A5), RN3.3 (R3.1)
unnamed: IC1.29 (A6), RN3.2 (R2.1)
unnamed: IC1.30 (A7), RN3.1 (R1.1)
unnamed: IC1.31 (A8), RN4.5 (R4.2)
unnamed: IC1.32 (A9), RN4.6 (R3.2)
unnamed: IC1.35 (CLK), R1.2
unnamed: IC1.39 (DQ8), RN2.8 (R8.1)
unnamed: IC1.40 (DQ9), RN2.7 (R7.1)
unnamed: IC1.42 (DQ10), RN2.6 (R6.1)
unnamed: IC1.43 (DQ11), RN2.5 (R5.1)
unnamed: IC1.45 (DQ12), RN2.4 (R4.1)
unnamed: IC1.46 (DQ13), RN2.3 (R3.1)
unnamed: IC1.48 (DQ14), RN2.2 (R2.1)
unnamed: IC1.49 (DQ15), RN2.1 (R1.1)
